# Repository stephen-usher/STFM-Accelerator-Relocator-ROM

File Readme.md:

This project is a PCB to allow two CPU sockets to be switched between on an
Atari ST.

It also provides a socket for a 512K ROM which can either be presented as a
single image or switched between an upper or lower image along with the logic
required to enable the larger ROMs, such as TOS 2.06 on a standard machine.

The ROM switching circuit was borrowed from Derkom (on the Exxos Forum) which
he used on his re-locator/switcher board for his STacy project.

The two sockets are identical so either can hold any processor which runs in a
68000 socket. On mine I currently had a stock 68000 in the "68000" socket and
a TF536 in the "Accelerator" one.

The ROM socket is compatible with the Exxos dual TOS ROMs.

P.S. There is another very important feature... there's a Turbo LED header,
which will light an LED if the "Accelerator" socket is in use.

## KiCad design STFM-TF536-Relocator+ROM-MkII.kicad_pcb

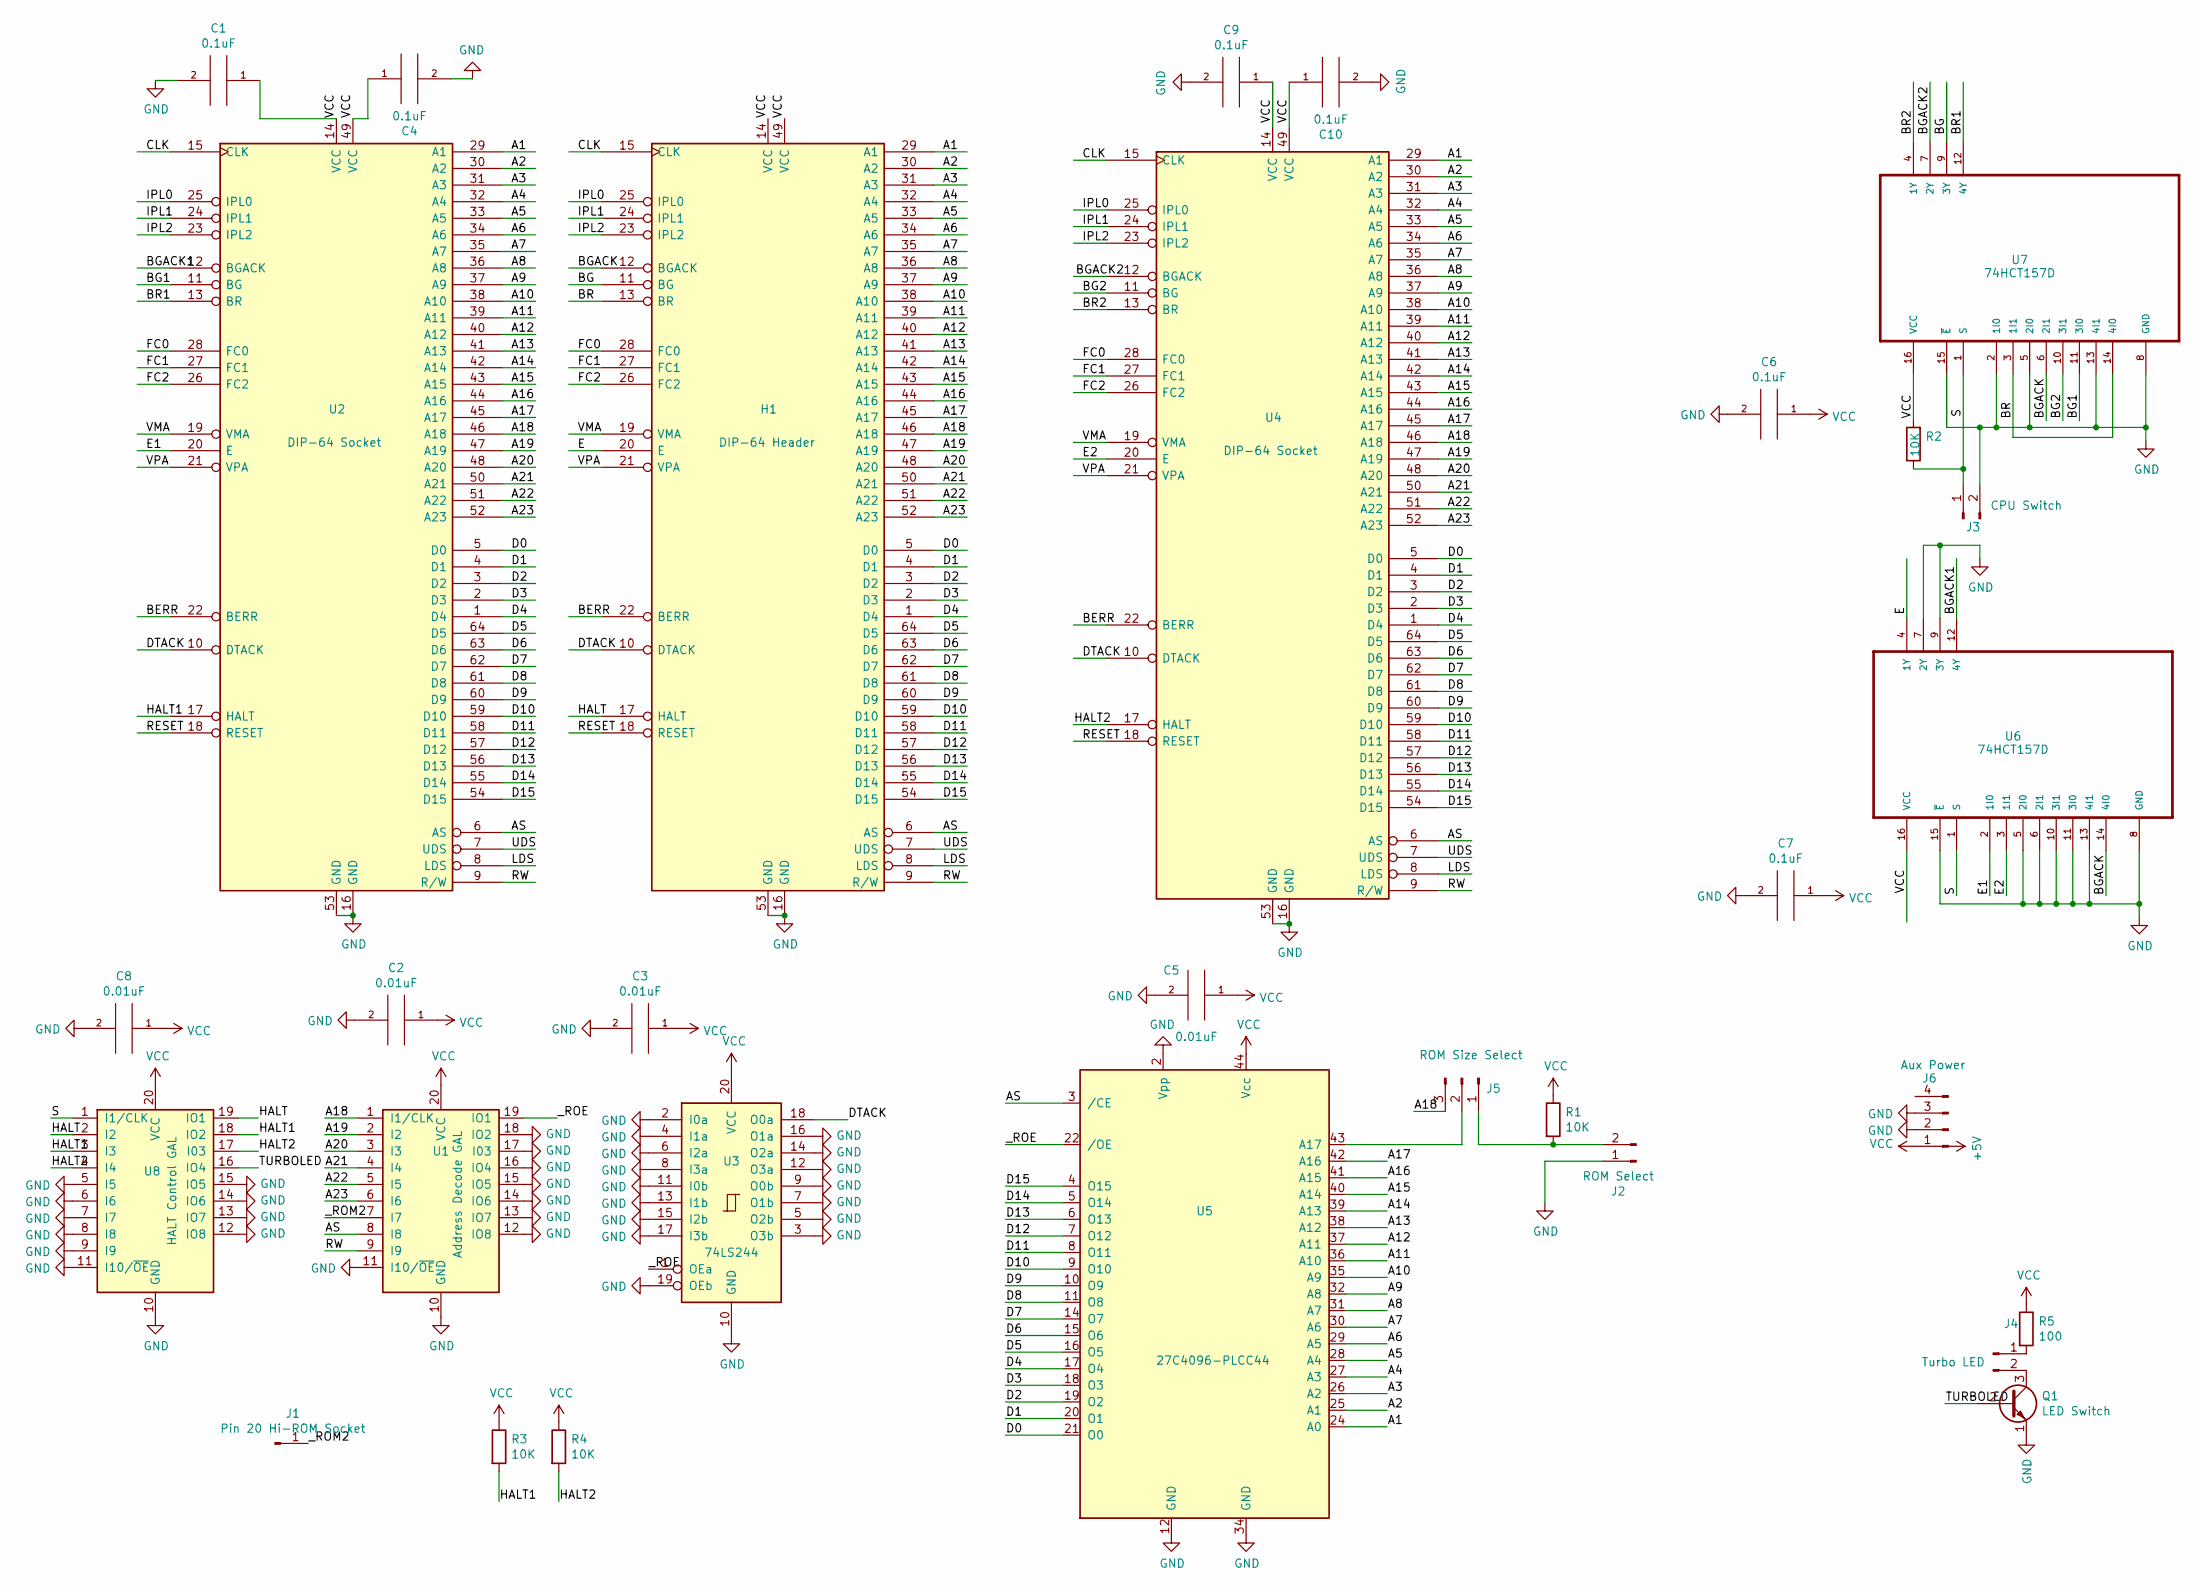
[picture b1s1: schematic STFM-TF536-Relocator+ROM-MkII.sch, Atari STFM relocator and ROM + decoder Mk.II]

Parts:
C1, C4, C6, C7, C9, C10: 0.1uF; C_0805_2012Metric
C2, C3, C5, C8: 0.01uF; C_0805_2012Metric
H1: DIP-64 Header; DIP-64_W22.86mm_Socket_LongPads
J1: Pin 20 Hi-ROM Socket; Pin_D1.0mm_L10.0mm
J2: ROM Select; PinHeader_1x02_P2.54mm_Horizontal
J3: CPU Switch; PinHeader_1x02_P2.54mm_Horizontal
J4: Turbo LED; PinHeader_1x02_P2.54mm_Horizontal
J5: ROM Size Select; PinHeader_1x03_P2.54mm_Horizontal
J6: Aux Power; PinHeader_1x04_P2.54mm_Horizontal
Q1: LED Switch; PinHeader_1x03_P2.54mm_Vertical
R1, R2, R3, R4: 10K; R_Axial_DIN0204_L3.6mm_D1.6mm_P7.62mm_Horizontal
R5: 100; R_Axial_DIN0204_L3.6mm_D1.6mm_P7.62mm_Horizontal
U1: Address Decode GAL; DIP-20_W7.62mm
U2, U4: DIP-64 Socket; DIP-64_W22.86mm_LongPads
U3: 74LS244; DIP-20_W7.62mm
U5: 27C4096-PLCC44; PLCC-44_THT-Socket
U6, U7: 74HCT157D; SO-16_3.9x9.9mm_P1.27mm
U8: HALT Control GAL; DIP-20_W7.62mm

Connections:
/A1: H1.29 (A1), U2.29 (A1), U4.29 (A1), U5.24 (A0)
/A2: H1.30 (A2), U2.30 (A2), U4.30 (A2), U5.25 (A1)
/A3: H1.31 (A3), U2.31 (A3), U4.31 (A3), U5.26 (A2)
/A4: H1.32 (A4), U2.32 (A4), U4.32 (A4), U5.27 (A3)
/A5: H1.33 (A5), U2.33 (A5), U4.33 (A5), U5.28 (A4)
/A6: H1.34 (A6), U2.34 (A6), U4.34 (A6), U5.29 (A5)
/A7: H1.35 (A7), U2.35 (A7), U4.35 (A7), U5.30 (A6)
/A8: H1.36 (A8), U2.36 (A8), U4.36 (A8), U5.31 (A7)
/A9: H1.37 (A9), U2.37 (A9), U4.37 (A9), U5.32 (A8)
/A10: H1.38 (A10), U2.38 (A10), U4.38 (A10), U5.35 (A9)
/A11: H1.39 (A11), U2.39 (A11), U4.39 (A11), U5.36 (A10)
/A12: H1.40 (A12), U2.40 (A12), U4.40 (A12), U5.37 (A11)
/A13: H1.41 (A13), U2.41 (A13), U4.41 (A13), U5.38 (A12)
/A14: H1.42 (A14), U2.42 (A14), U4.42 (A14), U5.39 (A13)
/A15: H1.43 (A15), U2.43 (A15), U4.43 (A15), U5.40 (A14)
/A16: H1.44 (A16), U2.44 (A16), U4.44 (A16), U5.41 (A15)
/A17: H1.45 (A17), U2.45 (A17), U4.45 (A17), U5.42 (A16)
/A18: H1.46 (A18), J5.3, U1.1 (I1/CLK), U2.46 (A18), U4.46 (A18)
/A19: H1.47 (A19), U1.2 (I2), U2.47 (A19), U4.47 (A19)
/A20: H1.48 (A20), U1.3 (I3), U2.48 (A20), U4.48 (A20)
/A21: H1.50 (A21), U1.4 (I4), U2.50 (A21), U4.50 (A21)
/A22: H1.51 (A22), U1.5 (I5), U2.51 (A22), U4.51 (A22)
/A23: H1.52 (A23), U1.6 (I6), U2.52 (A23), U4.52 (A23)
/AS: H1.6 (AS), U1.8 (I8), U2.6 (AS), U4.6 (AS), U5.3 (/CE)
/BERR: H1.22 (BERR), U2.22 (BERR), U4.22 (BERR)
/BG: H1.11 (BG), U7.9 (3Y)
/BG1: U2.11 (BG), U7.11 (3I0)
/BG2: U4.11 (BG), U7.10 (3I1)
/BGACK: H1.12 (BGACK), U6.14 (4I0), U7.6 (2I1)
/BGACK1: U2.12 (BGACK), U6.12 (4Y)
/BGACK2: U4.12 (BGACK), U7.7 (2Y)
/BR: H1.13 (BR), U7.3 (1I1), U7.14 (4I0)
/BR1: U2.13 (BR), U7.12 (4Y)
/BR2: U4.13 (BR), U7.4 (1Y)
/CLK: H1.15 (CLK), U2.15 (CLK), U4.15 (CLK)
/D0: H1.5 (D0), U2.5 (D0), U4.5 (D0), U5.21 (O0)
/D1: H1.4 (D1), U2.4 (D1), U4.4 (D1), U5.20 (O1)
/D2: H1.3 (D2), U2.3 (D2), U4.3 (D2), U5.19 (O2)
/D3: H1.2 (D3), U2.2 (D3), U4.2 (D3), U5.18 (O3)
/D4: H1.1 (D4), U2.1 (D4), U4.1 (D4), U5.17 (O4)
/D5: H1.64 (D5), U2.64 (D5), U4.64 (D5), U5.16 (O5)
/D6: H1.63 (D6), U2.63 (D6), U4.63 (D6), U5.15 (O6)
/D7: H1.62 (D7), U2.62 (D7), U4.62 (D7), U5.14 (O7)
/D8: H1.61 (D8), U2.61 (D8), U4.61 (D8), U5.11 (O8)
/D9: H1.60 (D9), U2.60 (D9), U4.60 (D9), U5.10 (O9)
/D10: H1.59 (D10), U2.59 (D10), U4.59 (D10), U5.9 (O10)
/D11: H1.58 (D11), U2.58 (D11), U4.58 (D11), U5.8 (O11)
/D12: H1.57 (D12), U2.57 (D12), U4.57 (D12), U5.7 (O12)
/D13: H1.56 (D13), U2.56 (D13), U4.56 (D13), U5.6 (O13)
/D14: H1.55 (D14), U2.55 (D14), U4.55 (D14), U5.5 (O14)
/D15: H1.54 (D15), U2.54 (D15), U4.54 (D15), U5.4 (O15)
/DTACK: H1.10 (DTACK), U2.10 (DTACK), U3.18 (O0a), U4.10 (DTACK)
/E: H1.20 (E), U6.4 (1Y)
/E1: U2.20 (E), U6.2 (1I0)
/E2: U4.20 (E), U6.3 (1I1)
/FC0: H1.28 (FC0), U2.28 (FC0), U4.28 (FC0)
/FC1: H1.27 (FC1), U2.27 (FC1), U4.27 (FC1)
/FC2: H1.26 (FC2), U2.26 (FC2), U4.26 (FC2)
/HALT: H1.17 (HALT), U8.2 (I2), U8.19 (IO1)
/HALT1: R3.2, U2.17 (HALT), U8.3 (I3), U8.18 (IO2)
/HALT2: R4.2, U4.17 (HALT), U8.4 (I4), U8.17 (I03)
/IPL0: H1.25 (IPL0), U2.25 (IPL0), U4.25 (IPL0)
/IPL1: H1.24 (IPL1), U2.24 (IPL1), U4.24 (IPL1)
/IPL2: H1.23 (IPL2), U2.23 (IPL2), U4.23 (IPL2)
/LDS: H1.8 (LDS), U2.8 (LDS), U4.8 (LDS)
/RESET: H1.18 (RESET), U2.18 (RESET), U4.18 (RESET)
/RW: H1.9 (R/W), U1.9 (I9), U2.9 (R/W), U4.9 (R/W)
/S: J3.1, R2.1, U6.1 (S), U7.1 (S), U8.1 (I1/CLK)
/TURBOLED: Q1.2 (B), U8.16 (IO4)
/UDS: H1.7 (UDS), U2.7 (UDS), U4.7 (UDS)
/VMA: H1.19 (VMA), U2.19 (VMA), U4.19 (VMA)
/VPA: H1.21 (VPA), U2.21 (VPA), U4.21 (VPA)
/_ROE: U1.19 (IO1), U3.1 (OEa), U5.22 (/OE)
/_ROM2: J1.1, U1.7 (I7)
GND: C1.2, C2.2, C3.2, C4.2, C5.2, C6.2, C7.2, C8.2, C9.2, C10.2, H1.16 (GND), H1.53 (GND), J2.1, J3.2, J6.2, J6.3, Q1.1 (E), U1.10 (GND), U1.11 (I10/~OE~), U1.12 (IO8), U1.13 (IO7), U1.14 (IO6), U1.15 (IO5), U1.16 (IO4), U1.17 (I03), U1.18 (IO2), U2.16 (GND), U2.53 (GND), U3.2 (I0a), U3.3 (O3b), U3.4 (I1a), U3.5 (O2b), U3.6 (I2a), U3.7 (O1b), U3.8 (I3a), U3.9 (O0b), U3.10 (GND), U3.11 (I0b), U3.12 (O3a), U3.13 (I1b), U3.14 (O2a), U3.15 (I2b), U3.16 (O1a), U3.17 (I3b), U3.19 (OEb), U4.16 (GND), U4.53 (GND), U5.2 (Vpp), U5.12 (GND), U5.34 (GND), U6.5 (2I0), U6.6 (2I1), U6.7 (2Y), U6.8 (GND), U6.9 (3Y), U6.10 (3I1), U6.11 (3I0), U6.13 (4I1), U6.15 (~E), U7.2 (1I0), U7.5 (2I0), U7.8 (GND), U7.13 (4I1), U7.15 (~E), U8.5 (I5), U8.6 (I6), U8.7 (I7), U8.8 (I8), U8.9 (I9), U8.10 (GND), U8.11 (I10/~OE~), U8.12 (IO8), U8.13 (IO7), U8.14 (IO6), U8.15 (IO5)
unnamed: J2.2, J5.1, R1.2
unnamed: J4.1, R5.2
unnamed: J4.2, Q1.3 (C)
unnamed: J5.2, U5.43 (A17)
VCC: C1.1, C2.1, C3.1, C4.1, C5.1, C6.1, C7.1, C8.1, C9.1, C10.1, H1.14 (VCC), H1.49 (VCC), J6.1, R1.1, R2.2, R3.1, R4.1, R5.1, U1.20 (VCC), U2.14 (VCC), U2.49 (VCC), U3.20 (VCC), U4.14 (VCC), U4.49 (VCC), U5.44 (Vcc), U6.16 (VCC), U7.16 (VCC), U8.20 (VCC)

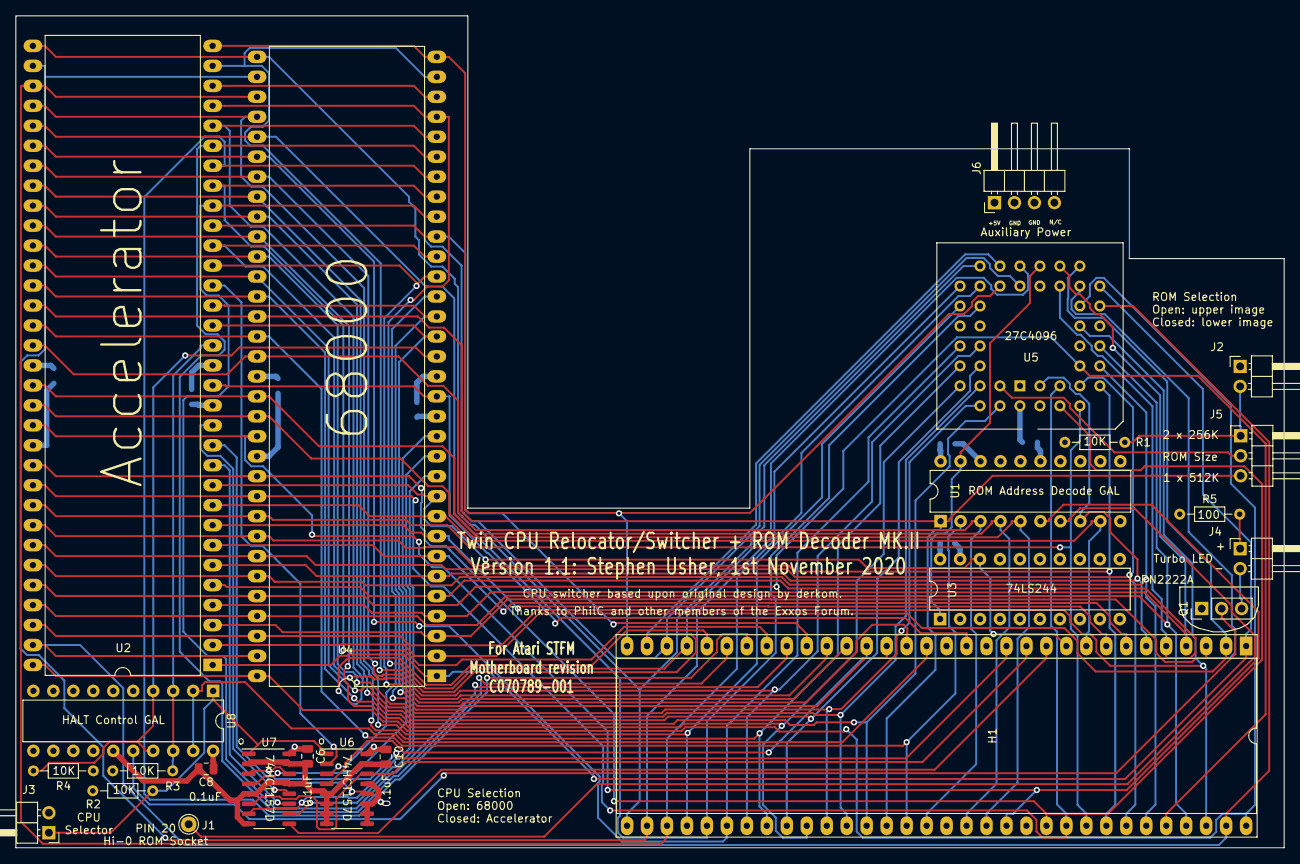
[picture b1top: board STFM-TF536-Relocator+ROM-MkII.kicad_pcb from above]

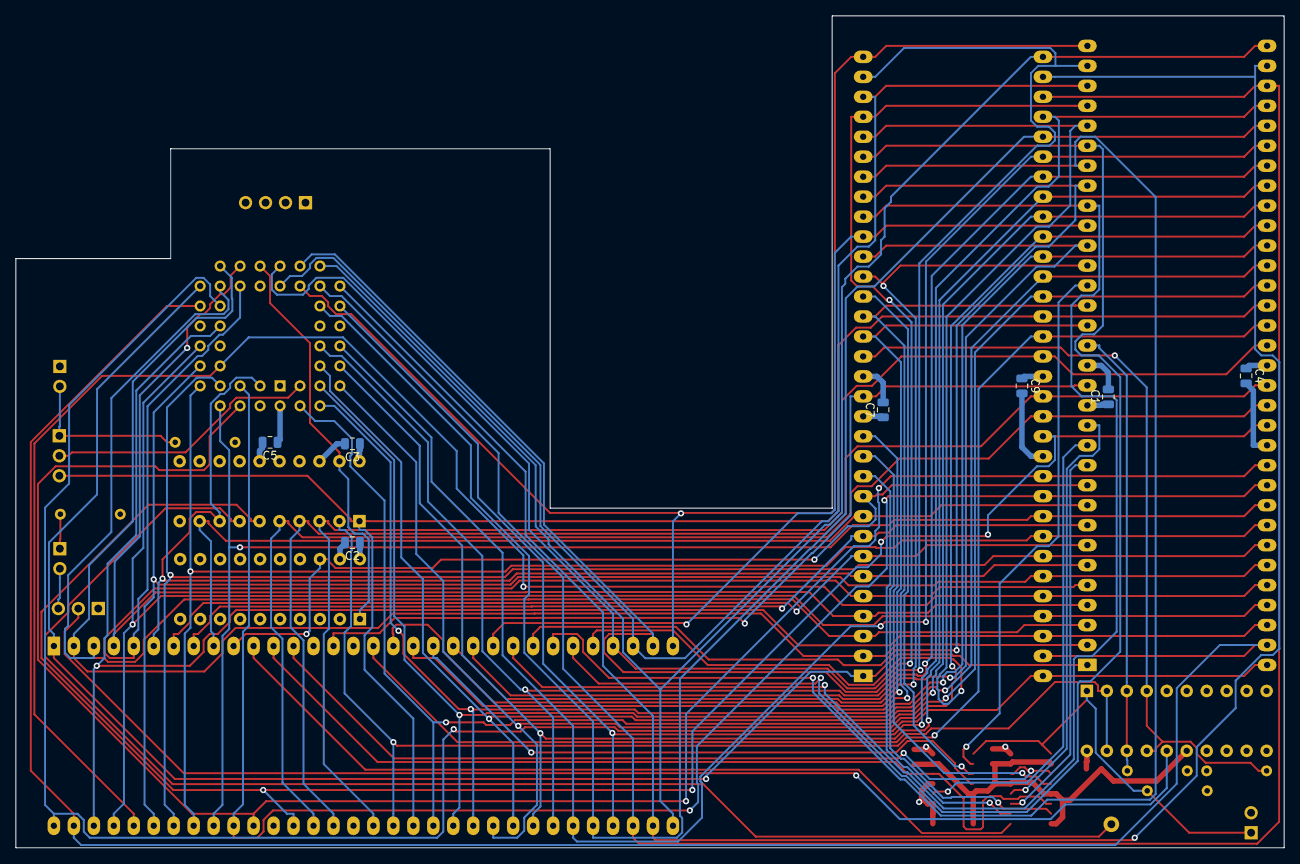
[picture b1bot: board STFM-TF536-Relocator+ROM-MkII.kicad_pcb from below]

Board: 4 copper layers, 161.3 x 105.8 mm, 31 parts (7 on the bottom side), 80 nets.

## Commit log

2021-09-28 Clean-up
2021-09-28 Cleaned up the files.
2021-09-28 Remove the NAS @eaDir directory.
